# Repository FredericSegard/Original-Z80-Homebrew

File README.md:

# Original Z80 Homebrew
 This is my original homebrew design

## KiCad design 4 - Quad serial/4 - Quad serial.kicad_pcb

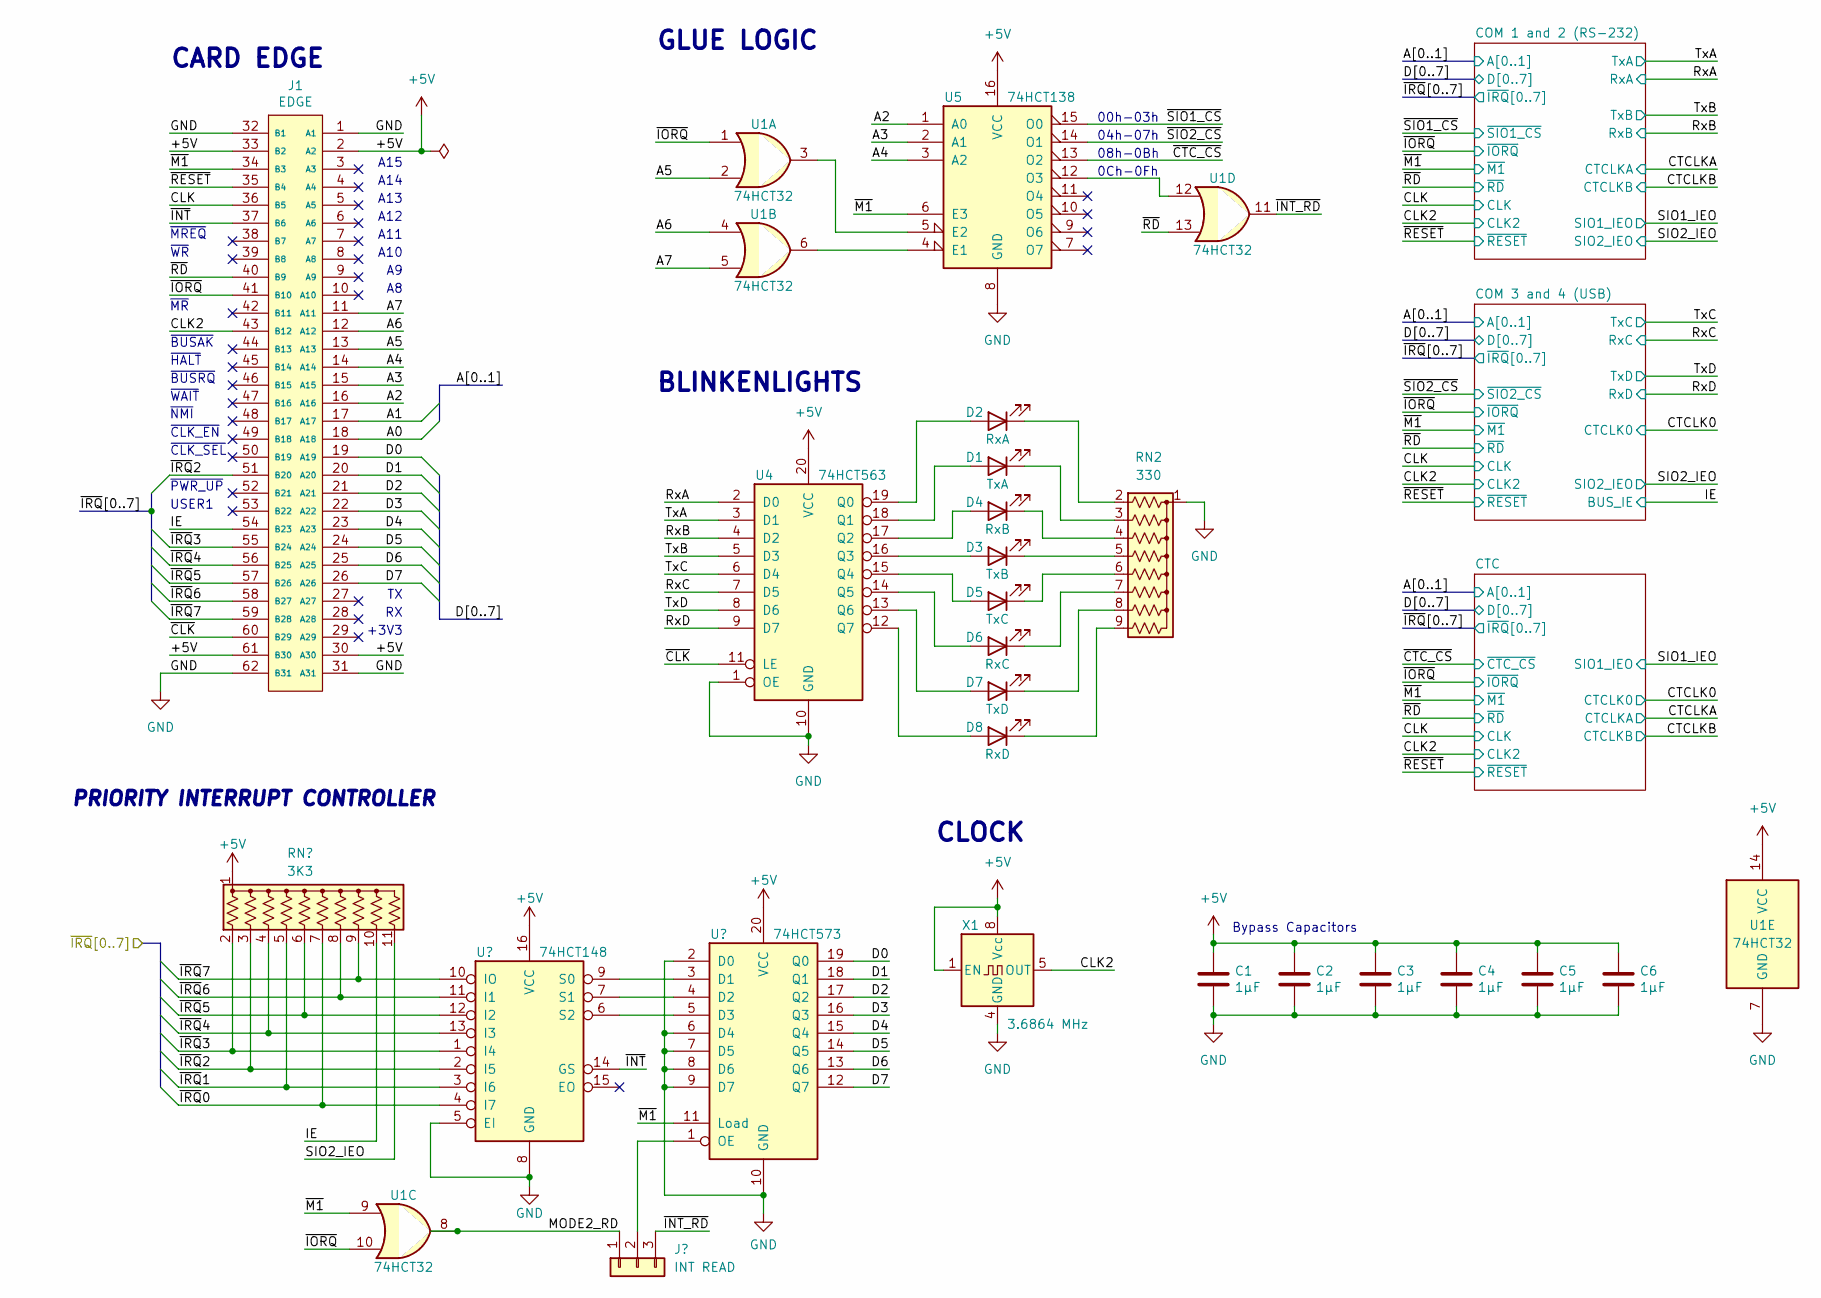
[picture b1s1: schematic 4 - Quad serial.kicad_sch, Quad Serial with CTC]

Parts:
C1, C2, C3, C4, C5, C6: 1µF; C_Disc_D3.0mm_W1.6mm_P2.50mm
D1: TxA; LED_D3.0mm_Horizontal_O1.27mm_Z2.0mm_Clear
D2: RxA; LED_D3.0mm_Horizontal_O1.27mm_Z2.0mm_Clear
D3: TxB; LED_D3.0mm_Horizontal_O1.27mm_Z2.0mm_Clear
D4: RxB; LED_D3.0mm_Horizontal_O1.27mm_Z2.0mm_Clear
D5: TxC; LED_D3.0mm_Horizontal_O1.27mm_Z2.0mm_Clear
D6: RxC; LED_D3.0mm_Horizontal_O1.27mm_Z2.0mm_Clear
D7: TxD; LED_D3.0mm_Horizontal_O1.27mm_Z2.0mm_Clear
D8: RxD; LED_D3.0mm_Horizontal_O1.27mm_Z2.0mm_Clear
J1: EDGE; BUS_XT_Proto; Mouser Part Number 571-6-5530843-5
J2: INT READ; PinHeader_1x03_P2.54mm_Vertical
RN1: 3K3; R_Array_SIP11
RN2: 330; R_Array_SIP9
U1: 74HCT32; DIP-14_W7.62mm_Socket
U2: 74HCT148; DIP-16_W7.62mm_Socket
U3: 74HCT573; DIP-20_W7.62mm_Socket
U4: 74HCT563; DIP-20_W7.62mm_Socket
U5: 74HCT138; DIP-16_W7.62mm_Socket
X1: 3.6864 MHz; DIP-8-4_W7.62mm_Oscillator_Socket

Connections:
+5V: C1.1, C2.1, C3.1, C4.1, C5.1, C6.1, J1.2 (A2), J1.30 (A30), J1.33 (B2), J1.61 (B30), RN1.1 (common), U1.14 (VCC), U2.16 (VCC), U3.20 (VCC), U4.20 (VCC), U5.16 (VCC), X1.1 (EN), X1.8 (Vcc); also elsewhere on the board
/A0: J1.18 (A18); also elsewhere on the board
/A1: J1.17 (A17); also elsewhere on the board
/A2: J1.16 (A16), U5.1 (A0)
/A3: J1.15 (A15), U5.2 (A1)
/A4: J1.14 (A14), U5.3 (A2)
/A5: J1.13 (A13), U1.2
/A6: J1.12 (A12), U1.4
/A7: J1.11 (A11), U1.5
/CLK: J1.36 (B5); also elsewhere on the board
/CLK2: J1.43 (B12), X1.5 (OUT); also elsewhere on the board
/D0: J1.19 (A19), U3.19 (Q0); also elsewhere on the board
/D1: J1.20 (A20), U3.18 (Q1); also elsewhere on the board
/D2: J1.21 (A21), U3.17 (Q2); also elsewhere on the board
/D3: J1.22 (A22), U3.16 (Q3); also elsewhere on the board
/D4: J1.23 (A23), U3.15 (Q4); also elsewhere on the board
/D5: J1.24 (A24), U3.14 (Q5); also elsewhere on the board
/D6: J1.25 (A25), U3.13 (Q6); also elsewhere on the board
/D7: J1.26 (A26), U3.12 (Q7); also elsewhere on the board
/IE: J1.54 (B23), RN1.10 (R9); also elsewhere on the board
/MODE2_RD: J2.1, U1.8
/RxA: U4.2 (D0); also elsewhere on the board
/RxB: U4.4 (D2); also elsewhere on the board
/RxC: U4.7 (D5); also elsewhere on the board
/RxD: U4.9 (D7); also elsewhere on the board
/SIO2_IEO: RN1.11 (R10); also elsewhere on the board
/TxA: U4.3 (D1); also elsewhere on the board
/TxB: U4.5 (D3); also elsewhere on the board
/TxC: U4.6 (D4); also elsewhere on the board
/TxD: U4.8 (D6); also elsewhere on the board
/~CLK: J1.60 (B29), U4.11 (LE)
/~CTC_CS: U5.13 (O2); also elsewhere on the board
/~INT_RD: J2.3, U1.11
/~INT: J1.37 (B6), U2.14 (GS)
/~IORQ: J1.41 (B10), U1.1, U1.10; also elsewhere on the board
/~IRQ0: RN1.7 (R6), U2.4 (I7); also elsewhere on the board
/~IRQ1: RN1.5 (R4), U2.3 (I6); also elsewhere on the board
/~IRQ2: J1.51 (B20), RN1.3 (R2), U2.2 (I5)
/~IRQ3: J1.55 (B24), RN1.2 (R1), U2.1 (I4)
/~IRQ4: J1.56 (B25), RN1.4 (R3), U2.13 (I3)
/~IRQ5: J1.57 (B26), RN1.6 (R5), U2.12 (I2)
/~IRQ6: J1.58 (B27), RN1.8 (R7), U2.11 (I1)
/~IRQ7: J1.59 (B28), RN1.9 (R8), U2.10 (IO)
/~M1: J1.34 (B3), U1.9, U3.11 (Load), U5.6 (E3); also elsewhere on the board
/~RD: J1.40 (B9), U1.13; also elsewhere on the board
/~RESET: J1.35 (B4); also elsewhere on the board
/~SIO1_CS: U5.15 (O0); also elsewhere on the board
/~SIO2_CS: U5.14 (O1); also elsewhere on the board
GND: C1.2, C2.2, C3.2, C4.2, C5.2, C6.2, J1.1 (A1), J1.31 (A31), J1.32 (B1), J1.62 (B31), RN2.1 (common), U1.7 (GND), U2.5 (EI), U2.8 (GND), U3.2 (D0), U3.6 (D4), U3.7 (D5), U3.8 (D6), U3.9 (D7), U3.10 (GND), U4.1 (OE), U4.10 (GND), U5.8 (GND), X1.4 (GND); also elsewhere on the board
unnamed: D1.2 (A), U4.18 (Q1)
unnamed: D1.1 (K), RN2.3 (R2)
unnamed: D2.2 (A), U4.19 (Q0)
unnamed: D2.1 (K), RN2.2 (R1)
unnamed: D3.2 (A), U4.16 (Q3)
unnamed: D3.1 (K), RN2.5 (R4)
unnamed: D4.2 (A), U4.17 (Q2)
unnamed: D4.1 (K), RN2.4 (R3)
unnamed: D5.2 (A), U4.15 (Q4)
unnamed: D5.1 (K), RN2.6 (R5)
unnamed: D6.2 (A), U4.14 (Q5)
unnamed: D6.1 (K), RN2.7 (R6)
unnamed: D7.2 (A), U4.13 (Q6)
unnamed: D7.1 (K), RN2.8 (R7)
unnamed: D8.2 (A), U4.12 (Q7)
unnamed: D8.1 (K), RN2.9 (R8)
unnamed: J2.2, U3.1 (OE)
unnamed: U2.9 (S0), U3.3 (D1)
unnamed: U2.7 (S1), U3.4 (D2)
unnamed: U2.6 (S2), U3.5 (D3)
unnamed: U1.6, U5.4 (E1)
unnamed: U1.3, U5.5 (E2)
unnamed: U1.12, U5.12 (O3)

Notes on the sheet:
PRIORITY INTERRUPT CONTROLLER
04h-07h
0Ch-0Fh
GLUE LOGIC
~{BUSAK}
+3V3
00h-03h
~{WR}
~{MR}
~{MREQ}
CARD EDGE
~{HALT}
BLINKENLIGHTS
CLOCK
~{CLK_EN}
USER1
~{BUSRQ}
~{WAIT}
~{PWR_UP}
~{CLK_SEL}
A12
A13
A14
A10
Bypass Capacitors
A15
~{NMI}
08h-0Bh
A11

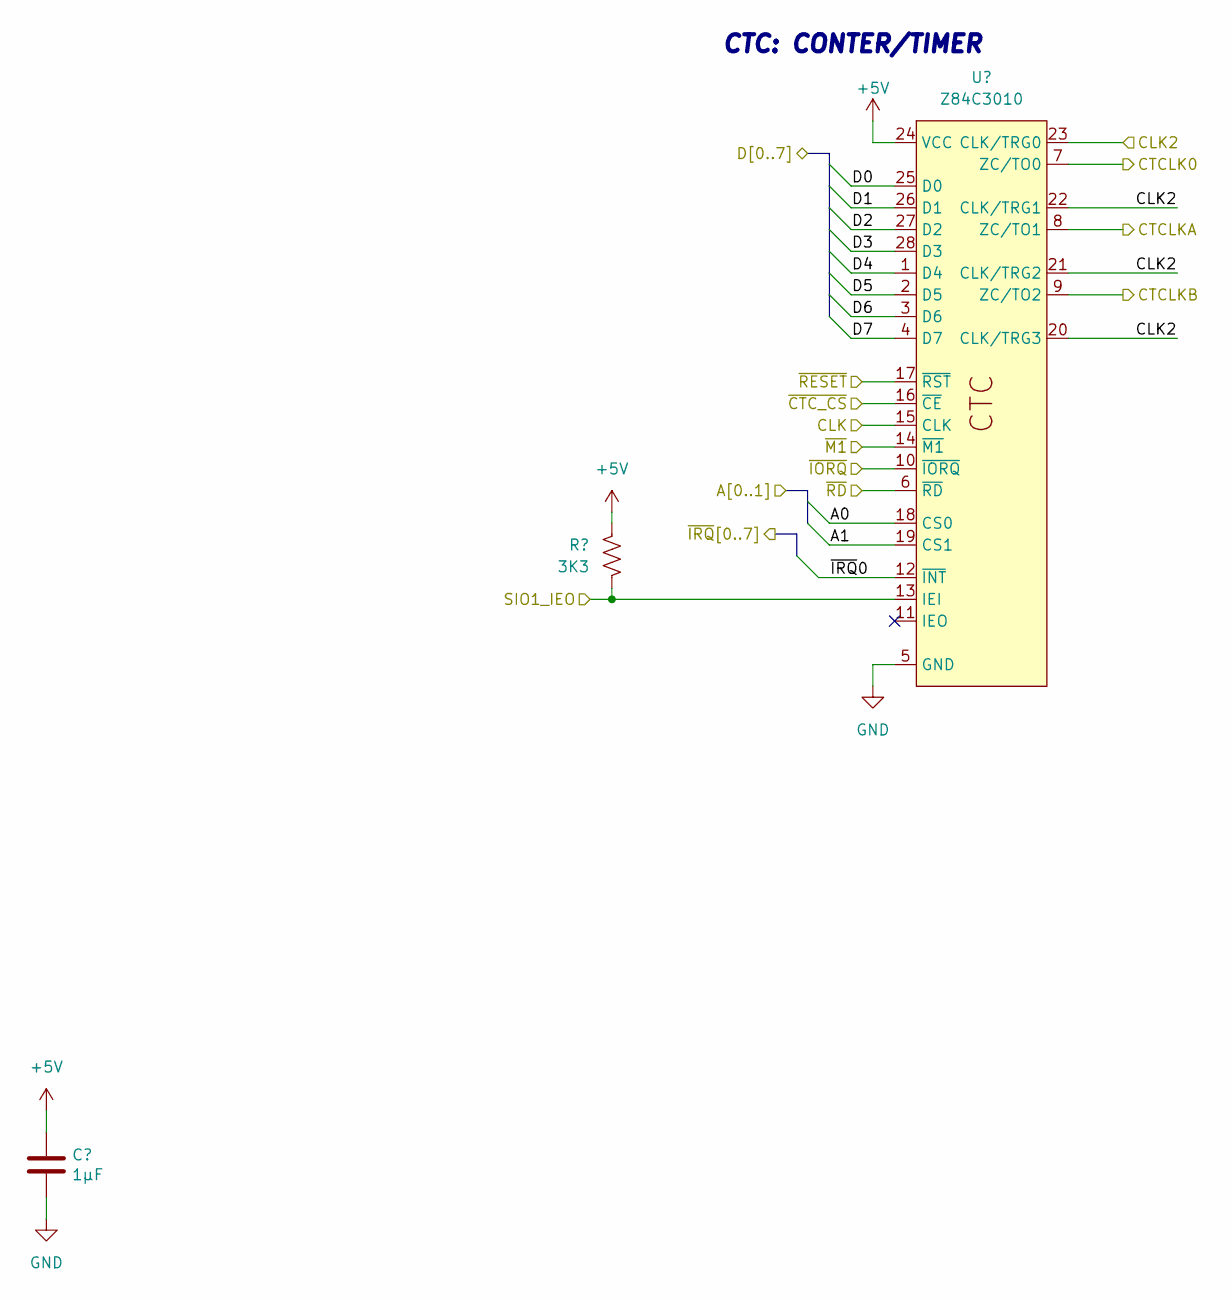
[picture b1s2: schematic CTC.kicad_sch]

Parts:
C23: 1µF; C_Disc_D3.0mm_W1.6mm_P2.50mm
R5: 3K3; R_Axial_DIN0207_L6.3mm_D2.5mm_P10.16mm_Horizontal
U12: Z84C3010; DIP-28_W15.24mm_Socket

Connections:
+5V: C23.1, R5.1, U12.24 (VCC); also elsewhere on the board
/A0: U12.18 (CS0); also elsewhere on the board
/A1: U12.19 (CS1); also elsewhere on the board
/CLK: U12.15 (CLK); also elsewhere on the board
/CLK2: U12.20 (CLK/TRG3), U12.21 (CLK/TRG2), U12.22 (CLK/TRG1), U12.23 (CLK/TRG0); also elsewhere on the board
/CTCLK0: U12.7 (ZC/TO0); also elsewhere on the board
/CTCLKA: U12.8 (ZC/TO1); also elsewhere on the board
/CTCLKB: U12.9 (ZC/TO2); also elsewhere on the board
/D0: U12.25 (D0); also elsewhere on the board
/D1: U12.26 (D1); also elsewhere on the board
/D2: U12.27 (D2); also elsewhere on the board
/D3: U12.28 (D3); also elsewhere on the board
/D4: U12.1 (D4); also elsewhere on the board
/D5: U12.2 (D5); also elsewhere on the board
/D6: U12.3 (D6); also elsewhere on the board
/D7: U12.4 (D7); also elsewhere on the board
/SIO1_IEO: R5.2, U12.13 (IEI); also elsewhere on the board
/~CTC_CS: U12.16 (~CE); also elsewhere on the board
/~IORQ: U12.10 (~IORQ); also elsewhere on the board
/~IRQ0: U12.12 (~INT); also elsewhere on the board
/~M1: U12.14 (~M1); also elsewhere on the board
/~RD: U12.6 (~RD); also elsewhere on the board
/~RESET: U12.17 (~RST); also elsewhere on the board
GND: C23.2, U12.5 (GND); also elsewhere on the board

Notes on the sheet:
CTC: CONTER/TIMER

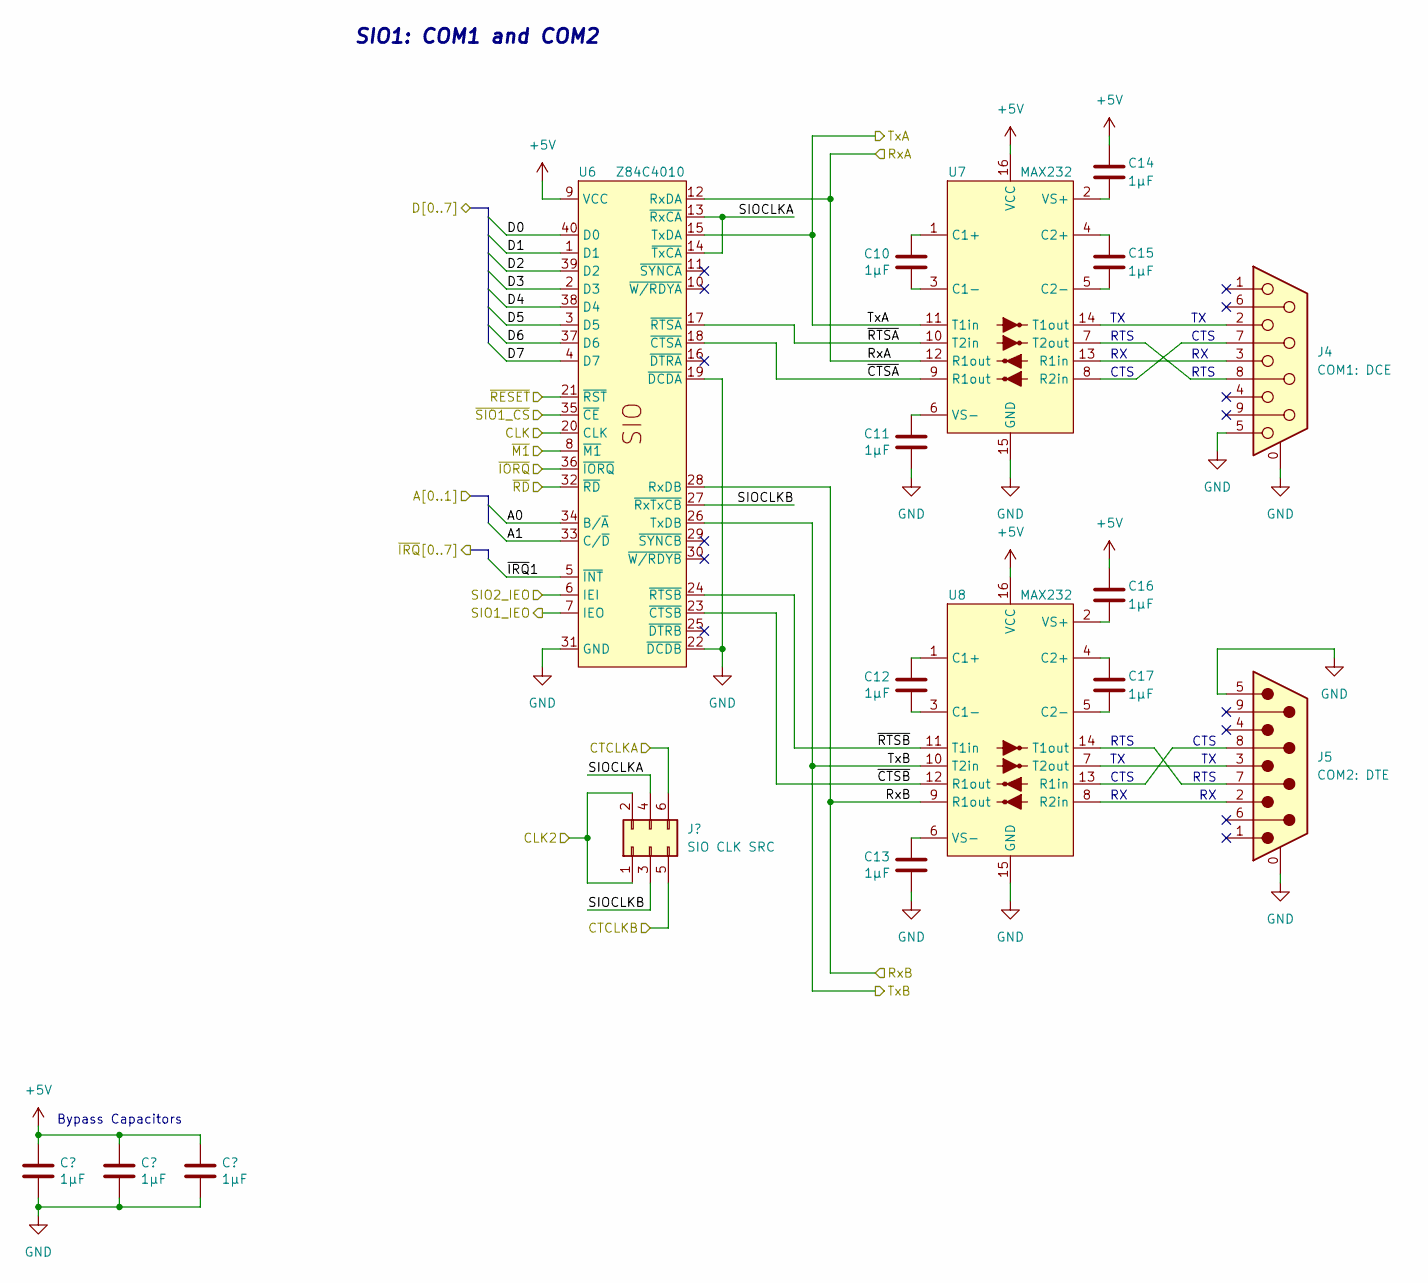
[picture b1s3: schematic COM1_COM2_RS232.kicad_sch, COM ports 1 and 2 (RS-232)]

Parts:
C7, C8, C9, C10, C11, C12, C13, C14, C15, C16, C17: 1µF; C_Disc_D3.0mm_W1.6mm_P2.50mm
J3: SIO CLK SRC; PinHeader_2x03_P2.54mm_Vertical
J4: COM1: DCE; DSUB-9_Female_Horizontal_P2.77x2.84mm_EdgePinOffset4.94mm_H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
J5: COM2: DTE; DSUB-9_Male_Horizontal_P2.77x2.84mm_EdgePinOffset4.94mm_Hou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
U6: Z84C4010; DIP-40_W15.24mm_Socket
U7, U8: MAX232; DIP-16_W7.62mm_Socket

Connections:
+5V: C7.1, C8.1, C9.1, C14.1, C16.1, U6.9 (VCC), U7.16 (VCC), U8.16 (VCC); also elsewhere on the board
/A0: U6.34 (B/~A); also elsewhere on the board
/A1: U6.33 (C/~D); also elsewhere on the board
/CLK: U6.20 (CLK); also elsewhere on the board
/CLK2: J3.1, J3.2; also elsewhere on the board
/COM 1 and 2 (RS-232)/SIOCLKA: J3.4, U6.13 (~RxCA), U6.14 (~TxCA)
/COM 1 and 2 (RS-232)/SIOCLKB: J3.3, U6.27 (~RxTxCB)
/COM 1 and 2 (RS-232)/~CTSA: U6.18 (~CTSA), U7.9 (R1out)
/COM 1 and 2 (RS-232)/~CTSB: U6.23 (~CTSB), U8.12 (R1out)
/COM 1 and 2 (RS-232)/~RTSA: U6.17 (~RTSA), U7.10 (T2in)
/COM 1 and 2 (RS-232)/~RTSB: U6.24 (~RTSB), U8.11 (T1in)
/CTCLKA: J3.6; also elsewhere on the board
/CTCLKB: J3.5; also elsewhere on the board
/D0: U6.40 (D0); also elsewhere on the board
/D1: U6.1 (D1); also elsewhere on the board
/D2: U6.39 (D2); also elsewhere on the board
/D3: U6.2 (D3); also elsewhere on the board
/D4: U6.38 (D4); also elsewhere on the board
/D5: U6.3 (D5); also elsewhere on the board
/D6: U6.37 (D6); also elsewhere on the board
/D7: U6.4 (D7); also elsewhere on the board
/RxA: U6.12 (RxDA), U7.12 (R1out); also elsewhere on the board
/RxB: U6.28 (RxDB), U8.9 (R1out); also elsewhere on the board
/SIO1_IEO: U6.7 (IEO); also elsewhere on the board
/SIO2_IEO: U6.6 (IEI); also elsewhere on the board
/TxA: U6.15 (TxDA), U7.11 (T1in); also elsewhere on the board
/TxB: U6.26 (TxDB), U8.10 (T2in); also elsewhere on the board
/~IORQ: U6.36 (~IORQ); also elsewhere on the board
/~IRQ1: U6.5 (~INT); also elsewhere on the board
/~M1: U6.8 (~M1); also elsewhere on the board
/~RD: U6.32 (~RD); also elsewhere on the board
/~RESET: U6.21 (~RST); also elsewhere on the board
/~SIO1_CS: U6.35 (~CE); also elsewhere on the board
GND: C7.2, C8.2, C9.2, C11.2, C13.2, J4.0 (PAD), J4.5, J5.0 (PAD), J5.5, U6.19 (~DCDA), U6.22 (~DCDB), U6.31 (GND), U7.15 (GND), U8.15 (GND); also elsewhere on the board
unnamed: C10.1, U7.1 (C1+)
unnamed: C10.2, U7.3 (C1-)
unnamed: C15.1, U7.4 (C2+)
unnamed: C15.2, U7.5 (C2-)
unnamed: J4.3, U7.13 (R1in)
unnamed: J4.7, U7.8 (R2in)
unnamed: J4.2, U7.14 (T1out)
unnamed: J4.8, U7.7 (T2out)
unnamed: C14.2, U7.2 (VS+)
unnamed: C11.1, U7.6 (VS-)
unnamed: C12.1, U8.1 (C1+)
unnamed: C12.2, U8.3 (C1-)
unnamed: C17.1, U8.4 (C2+)
unnamed: C17.2, U8.5 (C2-)
unnamed: J5.8, U8.13 (R1in)
unnamed: J5.2, U8.8 (R2in)
unnamed: J5.7, U8.14 (T1out)
unnamed: J5.3, U8.7 (T2out)
unnamed: C16.2, U8.2 (VS+)
unnamed: C13.1, U8.6 (VS-)

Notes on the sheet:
RTS
SIO1: COM1 and COM2
CTS
Bypass Capacitors

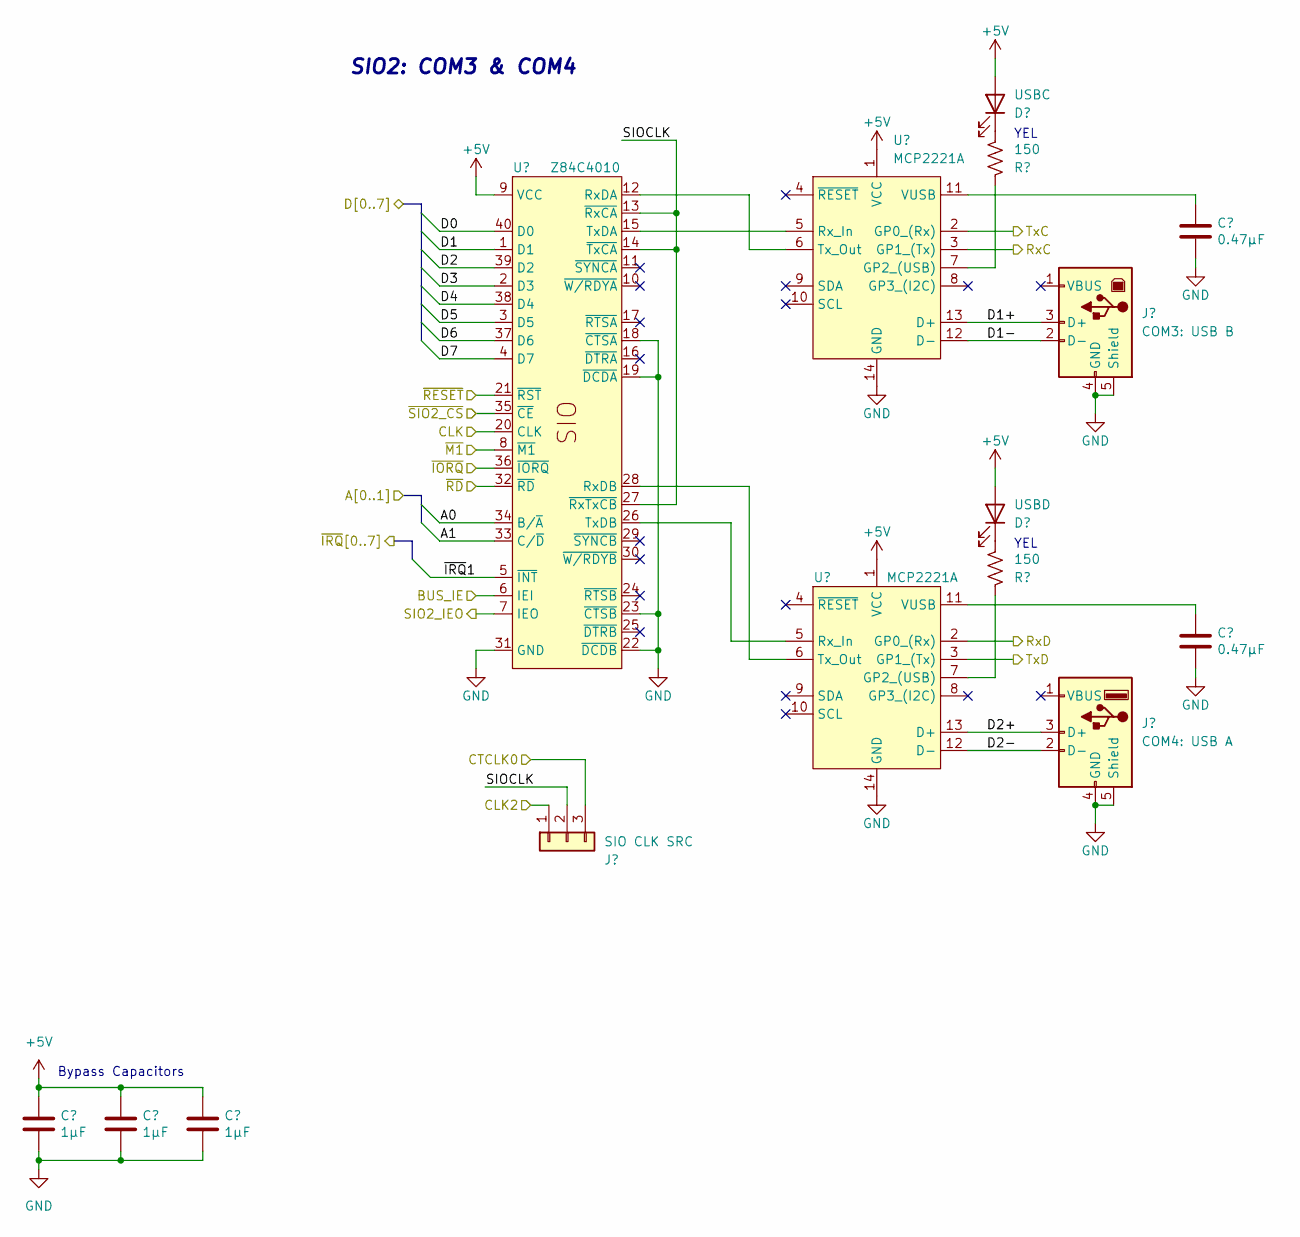
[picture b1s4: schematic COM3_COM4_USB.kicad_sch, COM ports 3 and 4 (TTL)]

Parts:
C18, C19, C20: 1µF; C_Disc_D3.0mm_W1.6mm_P2.50mm
C21, C22: 0.47µF; C_Disc_D3.0mm_W1.6mm_P2.50mm
D9: USBC; LED_D3.0mm_Horizontal_O1.27mm_Z2.0mm_Clear
D10: USBD; LED_D3.0mm_Horizontal_O1.27mm_Z2.0mm_Clear
J6: SIO CLK SRC; PinHeader_1x03_P2.54mm_Vertical
J7: COM3: USB B; USB_B_Lumberg_2411_02_Horizontal
J8: COM4: USB A; USB_A_Stewart_SS-52100-001_Horizontal
R3, R4: 150; R_Axial_DIN0207_L6.3mm_D2.5mm_P10.16mm_Horizontal
U9: Z84C4010; DIP-40_W15.24mm_Socket
U10, U11: MCP2221A; DIP-14_W7.62mm_Socket

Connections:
+5V: C18.1, C19.1, C20.1, D9.2 (A), D10.2 (A), U9.9 (VCC), U10.1 (VCC), U11.1 (VCC); also elsewhere on the board
/A0: U9.34 (B/~A); also elsewhere on the board
/A1: U9.33 (C/~D); also elsewhere on the board
/CLK: U9.20 (CLK); also elsewhere on the board
/CLK2: J6.1; also elsewhere on the board
/COM 3 and 4 (USB)/D1+: J7.3 (D+), U10.13 (D+)
/COM 3 and 4 (USB)/D1-: J7.2 (D-), U10.12 (D-)
/COM 3 and 4 (USB)/D2+: J8.3 (D+), U11.13 (D+)
/COM 3 and 4 (USB)/D2-: J8.2 (D-), U11.12 (D-)
/COM 3 and 4 (USB)/SIOCLK: J6.2, U9.13 (~RxCA), U9.14 (~TxCA), U9.27 (~RxTxCB)
/CTCLK0: J6.3; also elsewhere on the board
/D0: U9.40 (D0); also elsewhere on the board
/D1: U9.1 (D1); also elsewhere on the board
/D2: U9.39 (D2); also elsewhere on the board
/D3: U9.2 (D3); also elsewhere on the board
/D4: U9.38 (D4); also elsewhere on the board
/D5: U9.3 (D5); also elsewhere on the board
/D6: U9.37 (D6); also elsewhere on the board
/D7: U9.4 (D7); also elsewhere on the board
/IE: U9.6 (IEI); also elsewhere on the board
/RxC: U10.3 (GP1_(Tx)); also elsewhere on the board
/RxD: U11.2 (GP0_(Rx)); also elsewhere on the board
/SIO2_IEO: U9.7 (IEO); also elsewhere on the board
/TxC: U10.2 (GP0_(Rx)); also elsewhere on the board
/TxD: U11.3 (GP1_(Tx)); also elsewhere on the board
/~IORQ: U9.36 (~IORQ); also elsewhere on the board
/~IRQ1: U9.5 (~INT); also elsewhere on the board
/~M1: U9.8 (~M1); also elsewhere on the board
/~RD: U9.32 (~RD); also elsewhere on the board
/~RESET: U9.21 (~RST); also elsewhere on the board
/~SIO2_CS: U9.35 (~CE); also elsewhere on the board
GND: C18.2, C19.2, C20.2, C21.2, C22.2, J7.4 (GND), J7.5 (Shield), J8.4 (GND), J8.5 (Shield), U9.18 (~CTSA), U9.19 (~DCDA), U9.22 (~DCDB), U9.23 (~CTSB), U9.31 (GND), U10.14 (GND), U11.14 (GND); also elsewhere on the board
unnamed: D9.1 (K), R3.2
unnamed: D10.1 (K), R4.2
unnamed: R3.1, U10.7 (GP2_(USB))
unnamed: U9.15 (TxDA), U10.5 (Rx_In)
unnamed: U9.12 (RxDA), U10.6 (Tx_Out)
unnamed: C21.1, U10.11 (VUSB)
unnamed: R4.1, U11.7 (GP2_(USB))
unnamed: U9.26 (TxDB), U11.5 (Rx_In)
unnamed: U9.28 (RxDB), U11.6 (Tx_Out)
unnamed: C22.1, U11.11 (VUSB)

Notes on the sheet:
YEL
SIO2: COM3 & COM4
Bypass Capacitors

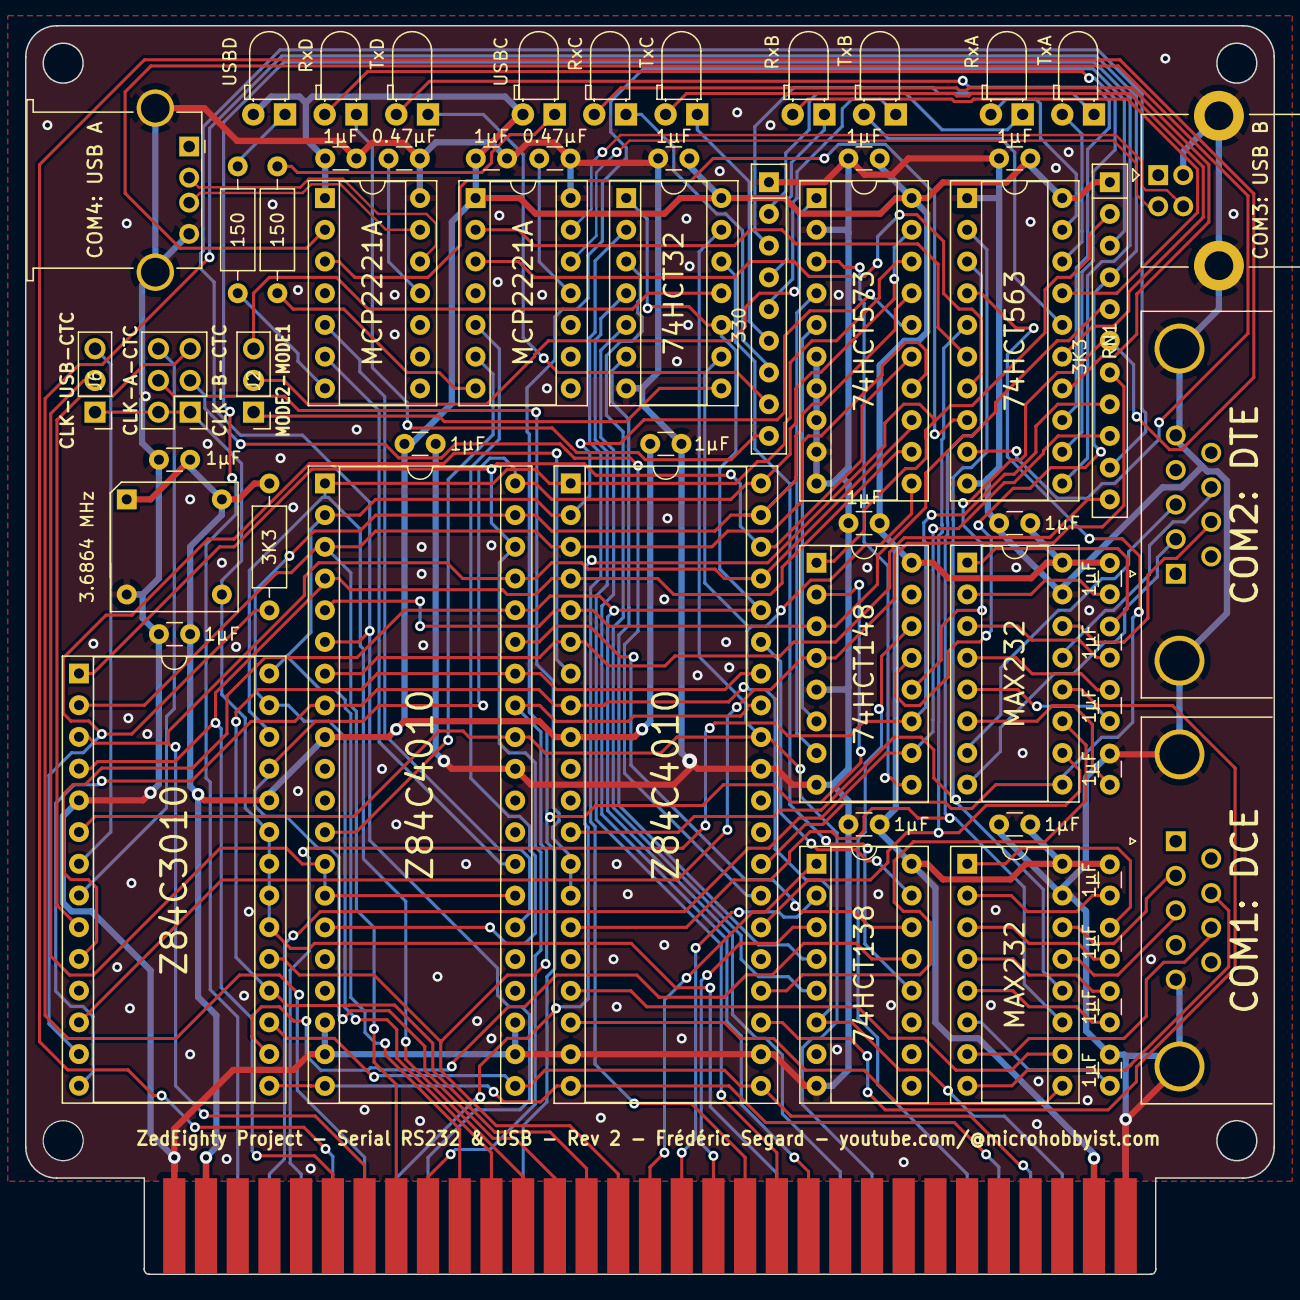
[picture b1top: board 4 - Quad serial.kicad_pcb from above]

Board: 2 copper layers, 100.0 x 100.0 mm, 59 parts (0 on the bottom side), 117 nets.
